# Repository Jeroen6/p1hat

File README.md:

# p1hat
Rasbperry Pi P1 Monitor (ztatz.nl) IO HAT

## Behuizing
Er is ook een behuizing!

## Aansluitingen

## Inputs

Er zijn 6 gebufferde ingangen geschikt voor open-collector apparaten.
Zoals S0 pulsen van energiemeters of NPN type inductieve sensoren voor watermeters.

Het buffer is een 74LVC07A met schmitt trigger ingangen en open drain uitgangen. 
Hiervoor is het dus nodig om de pull-ups in de BCM te activeren. 
Een ander buffer kan ook, velen passen op deze SOIC footprint.

Het filternetwerk 1k/1nF dempt eventuele ingekoppelde storingen en de sterke pull-up van 1 kOhm voorkomt spontane detecties. *(van nabij schakelende relais, motoren of andere storingen)*  

> Als er schakelaars worden aangesloten dient dit netwerk wellicht te worden vertraagd, probeer 100k en 10nf. Of [debounce](https://en.wikipedia.org/wiki/Switch#Contact_bounce) in software.

## Outputs

Twee smart high side fets kunnen bijna elke 12/45V last schakelen.
 - Ze zijn geschikt voor high-side switching. 
 - Ze zijn geschikt voor inductieve lasten zonder vrijloop diode. (relais)
 - Ze zijn thermisch kortsluitbeveiligd.
 
Vrijwel niet kapot te krijgen.

## RS-485

Op de print zit een RS-485 tranceiver. Om bijvoorbeeld te praten met RS-485 energiemeters.
De middelste pin van de RS-485 header is GND, dit is meestal niet nodig.

> Hoe dit op de raspberry werkt moet ik nog uitzoeken.  

## GPIO Header

| Board          | GPIO | Mode       |
|----------------|------|------------|
| IN1            | 17   | Pull-up    |
| IN2            | 27   | Pull-up    |
| IN3            | 22   | Pull-up    |
| IN4            | 23   | Pull-up    |
| IN5            | 24   | Pull-up    |
| IN6            | 25   | Pull-up    |
| OUT1           | 26   | Push-Pull  |
| OUT2           | 16   | Push-Pull  |
| RS485 TX       | 14   | Alt0       |
| RS485 RX       | 15   | Alt0       |
| RS485 TXENABLE | 18   | Push-Pull  |

## BOM

Lijst met onderdelen:

- PCB, zie .txt file in de map PCB voor onderdelen.
    - De onderdelen zijn te krijgen via Conrad, Reichelt of zelfs AliExpress of sinuss.nl (dat is farnell/avnet voor particulieren).
- Raspberry Pi 4 met SD kaart en P1 Monitor
- Behuizing 3D-geprint van PETG.
- Schroeven
    - 4x M2.5x16 Verzonken Torx (TX8) WS 9475TX
    - 4x M2.5x12 Verzonken Torx (TX8) WS 9475TX
        - Zie [rvspaleis.nl](https://www.rvspaleis.nl/bouten/torx/ws-9475/ws-9475-[-]-a2-[-]-m2,5)

> De 1 kOhm pull-ups parallel aan de LED heb ik op mijn print niet geplaatst. Mogelijk zijn deze bij andere typen, of geen, LED's wel nodig.

## Software

De gebruikte software is (gratis) Autodesk Fusion 360 voor niet-commercieel gebruik. 
De `*.f3z` bestanden zijn archieven hiervan.

## Suggesties of problemen?
Zet deze in de [Issues](https://github.com/Jeroen6/p1hat/issues) en vragen in [Discussions](https://github.com/Jeroen6/p1hat/discussions).

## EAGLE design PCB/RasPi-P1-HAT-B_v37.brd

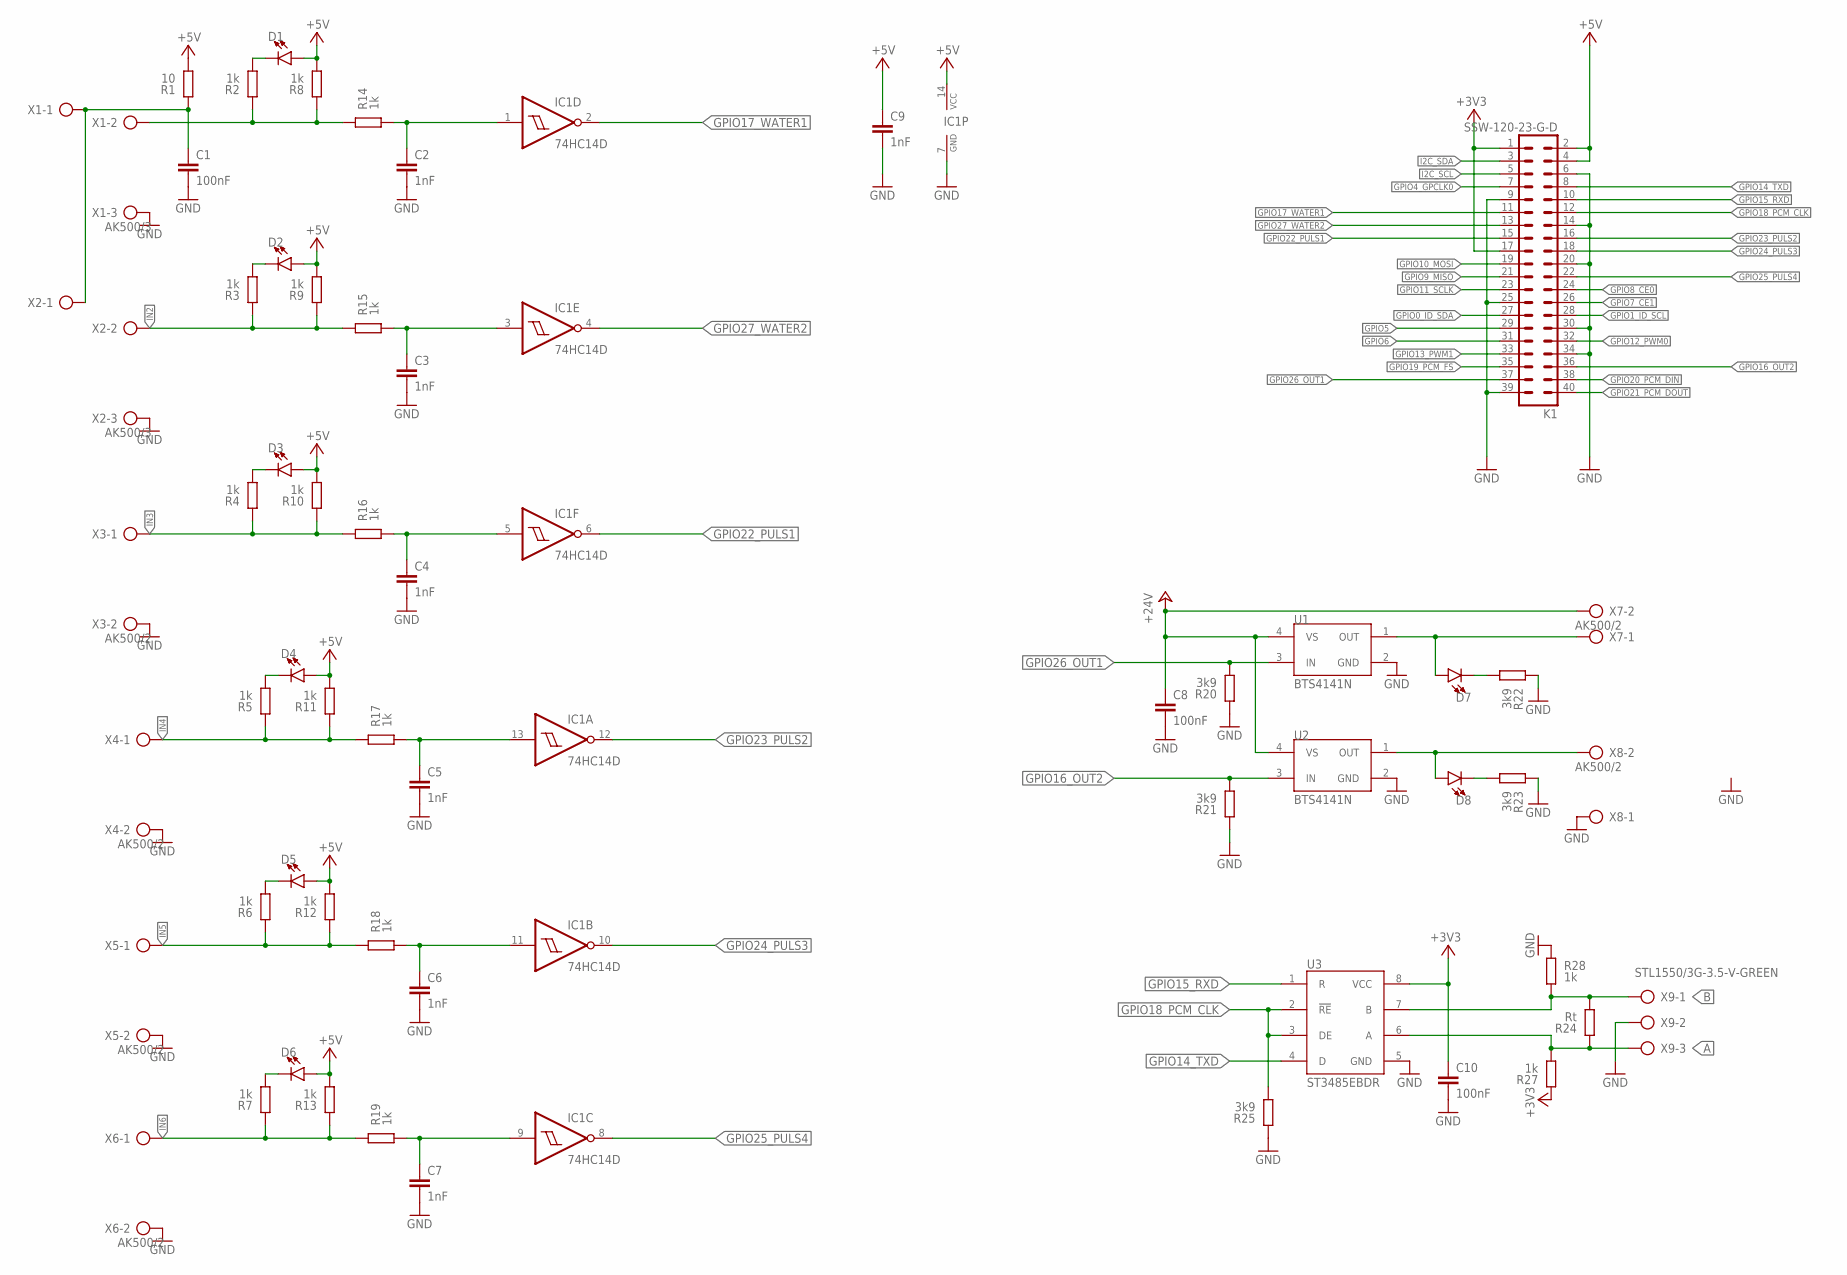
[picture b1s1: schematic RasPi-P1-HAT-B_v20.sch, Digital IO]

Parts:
C1, C8, C10: 100nF; C050-024X044
C2, C3, C4, C5, C6, C7, C9: 1nF; C050-024X044
D1, D2, D3, D4, D5, D6, D7, D8: LED3MM; LED_3MM
IC1: 74HC14D; SO14
K1: SSW-120-23-G-D; PIN_20X2
R1: 10; 0204/7; TOLERANCE 5%
R2, R3, R4, R5, R6, R7, R8, R9, R10, R11, R12, R13, R14, R15, R16, R17, R18, R19, R27, R28: 1k; 0204/7; TOLERANCE 5%
R20, R21, R22, R23, R25: 3k9; 0204/7; TOLERANCE 5%
R24: Rt; 0204/7; TOLERANCE 5%
U1, U2: BTS4141N; PG-SOT-223
U3: ST3485EBDR; SOIC-8
X1, X2: AK500/3
X3, X4, X5, X6, X7, X8: AK500/2
X9: STL1550/3G-3.5-V-GREEN; STL1550/3G-3.5-V-

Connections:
+3V3: C10.1, K1.1, K1.17, R27.2, U3.8 (VCC)
+5V: C9.1, D1.A, D2.A, D3.A, D4.A, D5.A, D6.A, IC1.14 (VCC), K1.2, K1.4, R1.1, R8.1, R9.1, R10.1, R11.1, R12.1, R13.1
+24V: C8.1, U1.4 (VS), U2.4 (VS), X7.2
A: R24.2, R27.1, U3.6 (A), X9.P$3
B: R24.1, R28.1, U3.7 (B), X9.P$1
GND: C1.2, C2.2, C3.2, C4.2, C5.2, C6.2, C7.2, C8.2, C9.2, C10.2, IC1.7 (GND), K1.6, K1.9, K1.14, K1.20, K1.25, K1.30, K1.34, K1.39, R20.2, R21.2, R22.2, R23.2, R25.2, R28.2, U1.2 (GND), U2.2 (GND), U3.5 (GND), X1.3, X2.3, X3.2, X4.2, X5.2, X6.2, X8.1, X9.P$2
GPIO0_ID_SDA: K1.27
GPIO1_ID_SCL: K1.28
GPIO4_GPCLK0: K1.7
GPIO5: K1.29
GPIO6: K1.31
GPIO7_CE1: K1.26
GPIO8_CE0: K1.24
GPIO9_MISO: K1.21
GPIO10_MOSI: K1.19
GPIO11_SCLK: K1.23
GPIO12_PWM0: K1.32
GPIO13_PWM1: K1.33
GPIO14_TXD: K1.8, U3.4 (D)
GPIO15_RXD: K1.10, U3.1 (R)
GPIO16_OUT2: K1.36, R21.1, U2.3 (IN)
GPIO17_WATER1: IC1.2 (O), K1.11
GPIO18_PCM_CLK: K1.12, R25.1, U3.2 (!RE), U3.3 (DE)
GPIO19_PCM_FS: K1.35
GPIO20_PCM_DIN: K1.38
GPIO21_PCM_DOUT: K1.40
GPIO22_PULS1: IC1.6 (O), K1.15
GPIO23_PULS2: IC1.12 (O), K1.16
GPIO24_PULS3: IC1.10 (O), K1.18
GPIO25_PULS4: IC1.8 (O), K1.22
GPIO26_OUT1: K1.37, R20.1, U1.3 (IN)
GPIO27_WATER2: IC1.4 (O), K1.13
I2C_SCL: K1.5
I2C_SDA: K1.3
IN1: R2.2, R8.2, R14.2, X1.2
IN1_1: C2.1, IC1.1 (I), R14.1
IN2: R3.2, R9.2, R15.2, X2.2
IN2_1: C3.1, IC1.3 (I), R15.1
IN3: R4.2, R10.2, R16.2, X3.1
IN3_1: C4.1, IC1.5 (I), R16.1
IN4: R5.2, R11.2, R17.2, X4.1
IN5: R6.2, R12.2, R18.2, X5.1
IN6: R7.2, R13.2, R19.2, X6.1
unnamed: D6.K (C), R7.1
unnamed: D5.K (C), R6.1
unnamed: D4.K (C), R5.1
unnamed: D7.K (C), R22.1
unnamed: D8.K (C), R23.1
unnamed: D3.K (C), R4.1
unnamed: D2.K (C), R3.1
unnamed: D1.K (C), R2.1
unnamed: C5.1, IC1.13 (I), R17.1
unnamed: C6.1, IC1.11 (I), R18.1
unnamed: C7.1, IC1.9 (I), R19.1
unnamed: C1.1, R1.2, X1.1, X2.1
OUT1: D7.A, U1.1 (OUT), X7.1
OUT2: D8.A, U2.1 (OUT), X8.2

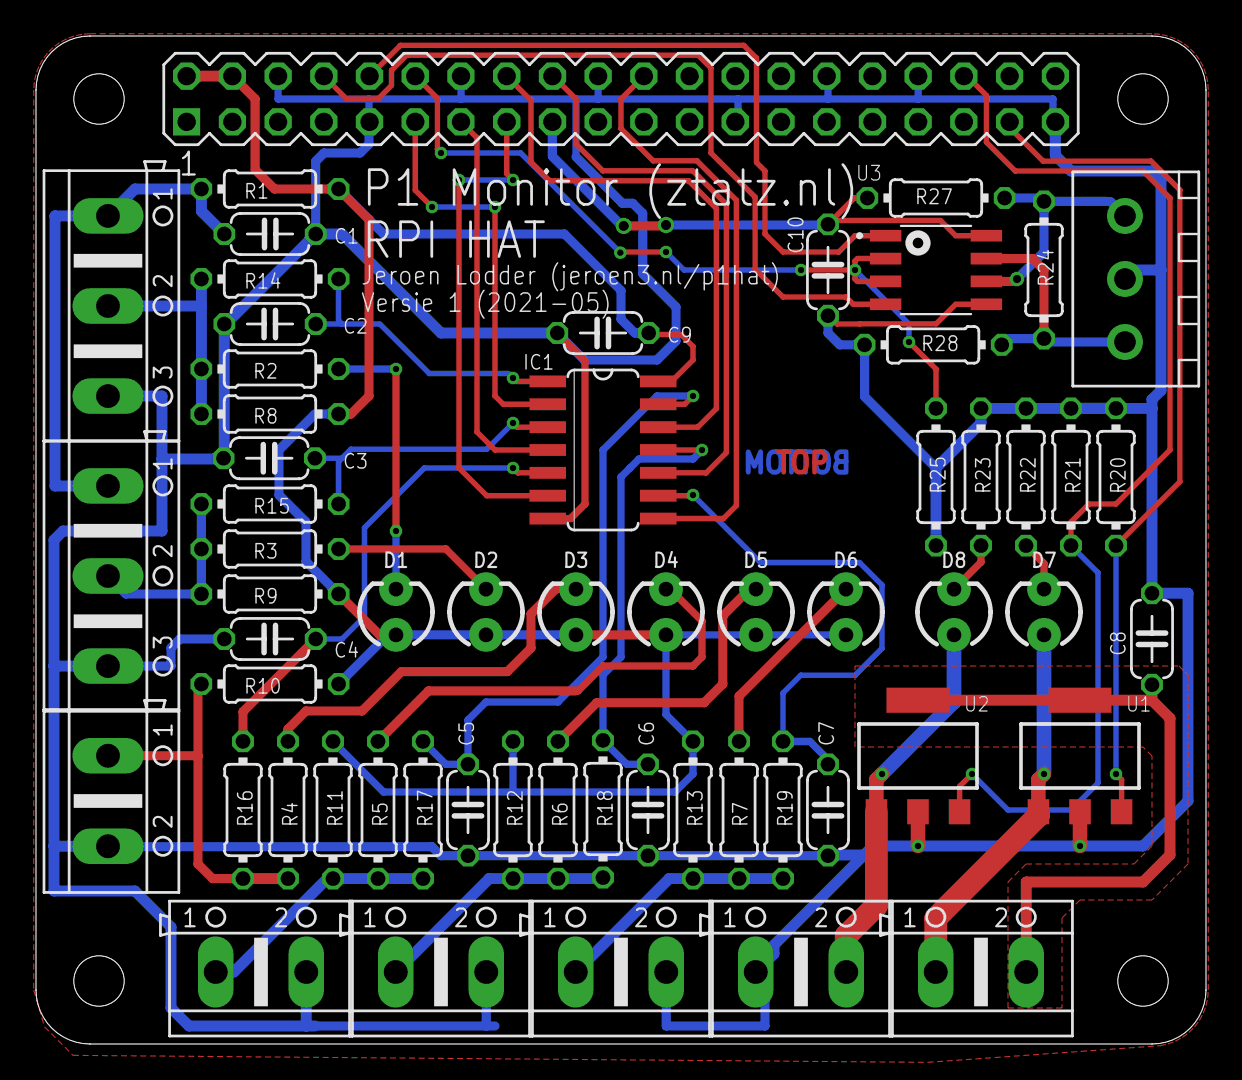
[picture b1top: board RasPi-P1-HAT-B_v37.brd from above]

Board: 2 copper layers, 65.0 x 56.0 mm, 60 parts (1 on the bottom side), 40 nets.

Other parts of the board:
U$3: MUELLTONNE_10.00

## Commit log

2021-06-23 Upload data
2021-07-03 Middendeel behuizing verhoogd vanwege onjuiste maat rpi header
2021-07-03 Foto behuizing
2021-07-07 aansluitschema
2021-09-27 Update filenames
2021-11-23 add gerber zip archive for pcb ordering
